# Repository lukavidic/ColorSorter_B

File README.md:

# Color Sorter | Real-Time Tile Sorting 🟥🟩🟦

## Project Specification

The project owner has defined the following general requirements:

- Detect and sort tiles by color using a sensor-based system.  
- Develop a PC application that provides Wi-Fi communication, real-time visualization, and process control.  
- Include a local physical interface for basic start/stop control.

## Project Objective

The goal of this project is to sort colored tiles into two designated containers. The system includes:

- **PIC24FJ64GA702 MCU** on a custom PCB,  
- **Color 10 Click sensor** for color detection,  
- **SG90 servo motor** to direct each tile into its container,  
- **ESP8266-01 Wi-Fi module** for wireless link to PC,  
- **Push-button** to toggle the sorting cycle on/off,  
- **LED indicator** to show system status.  

When a tile passes under the Color 10 Click sensor, it measures the color and sends the data via I²C to the MCU.

Based on the sorting logic, the MCU drives the servo to move the tile into the correct container.

The push-button starts and stops the cycle, while the LED indicates whether the system is active.

A PC application offers a graphical interface for live monitoring and control. It communicates with the ESP8266-01 over Wi-Fi, which forwards commands to the microcontroller using UART protocol.

## Additional Information

For detailed component specifications, wiring diagrams, datasheets and code documentation please see the Wiki pages in this repository.

## Project Video Presentation

[Video](https://github.com/lukavidic/ColorSorter_B/blob/project/video/ColorSorterB.mp4)

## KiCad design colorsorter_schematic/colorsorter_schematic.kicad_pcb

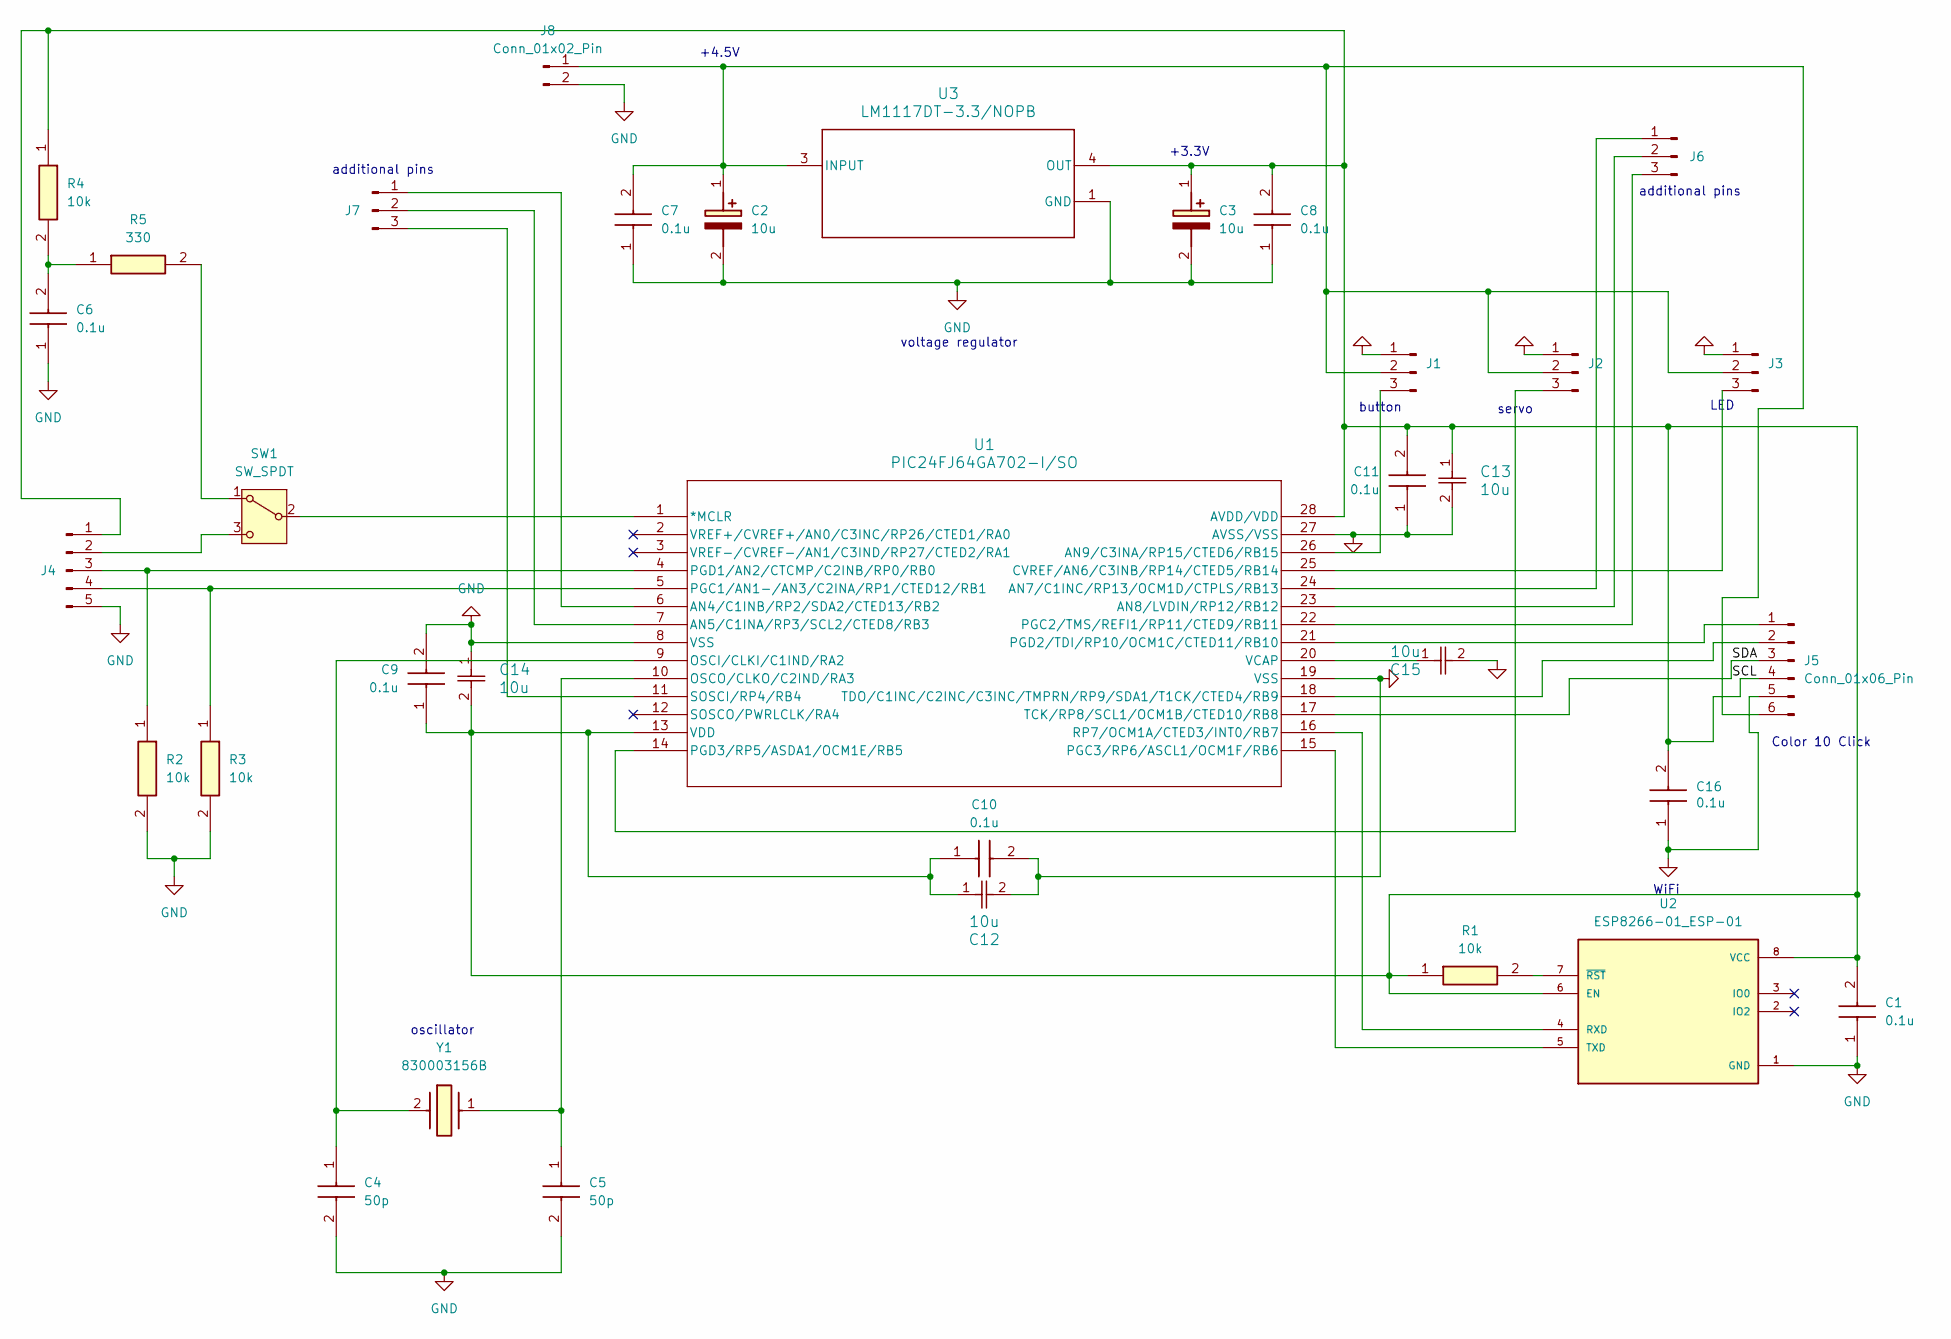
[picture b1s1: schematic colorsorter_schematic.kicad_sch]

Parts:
C1, C6, C7, C8, C9, C10, C11, C16: 0.1u; CAPC2012X94N; Manufacturer_Part_Number KAM21BR71H104JT; Mouser Part Number 581-KAM21BR71H104JT
C2, C3: 10u; CAPPM6032X280N; Manufacturer_Part_Number 293D106X9010C2TE3; Mouser Part Number 74-293D106X9010C2TE3
C4, C5: 50p; CAPC2012X140N; Manufacturer_Part_Number 08055A500FAT2A; Mouser Part Number 581-08055A500FAT2A
C12, C13, C14, C15: 10u; CAP_2012_TDK
J1, J2, J3, J6, J7: Conn_01x03_Pin; PinHeader_1x03_P2.54mm_Vertical
J4: Conn_01x05_Pin; PinHeader_1x05_P2.54mm_Vertical
J5: Conn_01x06_Pin; PinHeader_1x06_P2.54mm_Vertical
J8: Conn_01x02_Pin; PinHeader_1x02_P2.54mm_Vertical
R1, R2, R3, R4: 10k; RESC2012X70N; Manufacturer_Part_Number ERJ-S06F1002V; Mouser Part Number 667-ERJ-S06F1002V
R5: 330; ERJP06D1000V; Manufacturer_Part_Number ERJ-P06D3300V; Mouser Part Number 667-ERJ-P06D3300V
SW1: SW_SPDT; SLW12768644AD
U1: PIC24FJ64GA702-I/SO; SOIC28__SO28_MCH
U2: ESP8266-01_ESP-01; wifi; PARTREV V1.2
U3: LM1117DT-3.3/NOPB; NDP0003B
Y1: 830003156B; Manufacturer_Part_Number 830003156B; Mouser Part Number 710-830003156B

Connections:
/SCL: J5.3, U1.17 (TCK/RP8/SCL1/OCM1B/CTED10/RB8); also elsewhere on the board
GND: C1.1, C2.2 (-), C3.2 (-), C4.2, C5.2, C6.1, C7.1, C8.1, C9.2, C10.2, C11.1, C12.2, C13.2, C14.1, C15.2, C16.1, J1.1, J2.1, J3.1, J4.5, J5.5, J8.2, R2.2, R3.2, U1.8 (VSS), U1.19 (VSS), U1.27 (AVSS/VSS), U2.1 (GND), U3.1 (GND); also elsewhere on the board
unnamed: C2.1 (+), C7.2, J1.2, J2.2, J3.2, J5.6, J8.1, U3.3 (INPUT)
unnamed 3: C1.2, C3.1 (+), C8.2, C9.1, C10.1, C11.2, C12.1, C13.1, C14.2, C16.2, J4.1, J5.4, R1.1, R4.1, U1.13 (VDD), U1.28 (AVDD/VDD), U2.6 (EN), U2.8 (VCC), U3.4 (OUT); also elsewhere on the board
unnamed: C6.2, R4.2, R5.1
unnamed 5: J1.3, U1.26 (AN9/C3INA/RP15/CTED6/RB15); also elsewhere on the board
unnamed 6: J2.3, U1.14 (PGD3/RP5/ASDA1/OCM1E/RB5); also elsewhere on the board
unnamed 7: J3.3, U1.25 (CVREF/AN6/C3INB/RP14/CTED5/RB14); also elsewhere on the board
unnamed: J4.2, SW1.3 (C)
unnamed 9: J4.3, R2.1, U1.4 (PGD1/AN2/CTCMP/C2INB/RP0/RB0); also elsewhere on the board
unnamed 10: J4.4, R3.1, U1.5 (PGC1/AN1-/AN3/C2INA/RP1/CTED12/RB1); also elsewhere on the board
unnamed 11: J5.1, U1.21 (PGD2/TDI/RP10/OCM1C/CTED11/RB10); also elsewhere on the board
unnamed 12: J5.2, U1.18 (TDO/C1INC/C2INC/C3INC/TMPRN/RP9/SDA1/T1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); also elsewhere on the board
unnamed 13: J6.1, U1.24 (AN7/C1INC/RP13/OCM1D/CTPLS/RB13); also elsewhere on the board
unnamed 14: J6.2, U1.23 (AN8/LVDIN/RP12/RB12); also elsewhere on the board
unnamed 15: J6.3, U1.22 (PGC2/TMS/REFI1/RP11/CTED9/RB11); also elsewhere on the board
unnamed 16: J7.1, U1.6 (AN4/C1INB/RP2/SDA2/CTED13/RB2); also elsewhere on the board
unnamed 17: J7.2, U1.7 (AN5/C1INA/RP3/SCL2/CTED8/RB3); also elsewhere on the board
unnamed 18: J7.3, U1.11 (SOSCI/RP4/RB4); also elsewhere on the board
unnamed: R5.2, SW1.1 (A)
unnamed 20: SW1.2 (B), U1.1 (*MCLR); also elsewhere on the board
unnamed 21: C4.1, U1.9 (OSCI/CLKI/C1IND/RA2), Y1.2 (CRYSTAL_2); also elsewhere on the board
unnamed 22: C5.1, U1.10 (OSCO/CLKO/C2IND/RA3), Y1.1; also elsewhere on the board
unnamed 23: U1.15 (PGC3/RP6/ASCL1/OCM1F/RB6), U2.5 (TXD); also elsewhere on the board
unnamed 24: U1.16 (RP7/OCM1A/CTED3/INT0/RB7), U2.4 (RXD); also elsewhere on the board
unnamed 25: C15.1, U1.20 (VCAP); also elsewhere on the board
unnamed: R1.2, U2.7 (~RST)

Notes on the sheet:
additional pins
LED
oscillator
+3.3V
+4.5V
servo
WiFi
voltage regulator
button
Color 10 Click

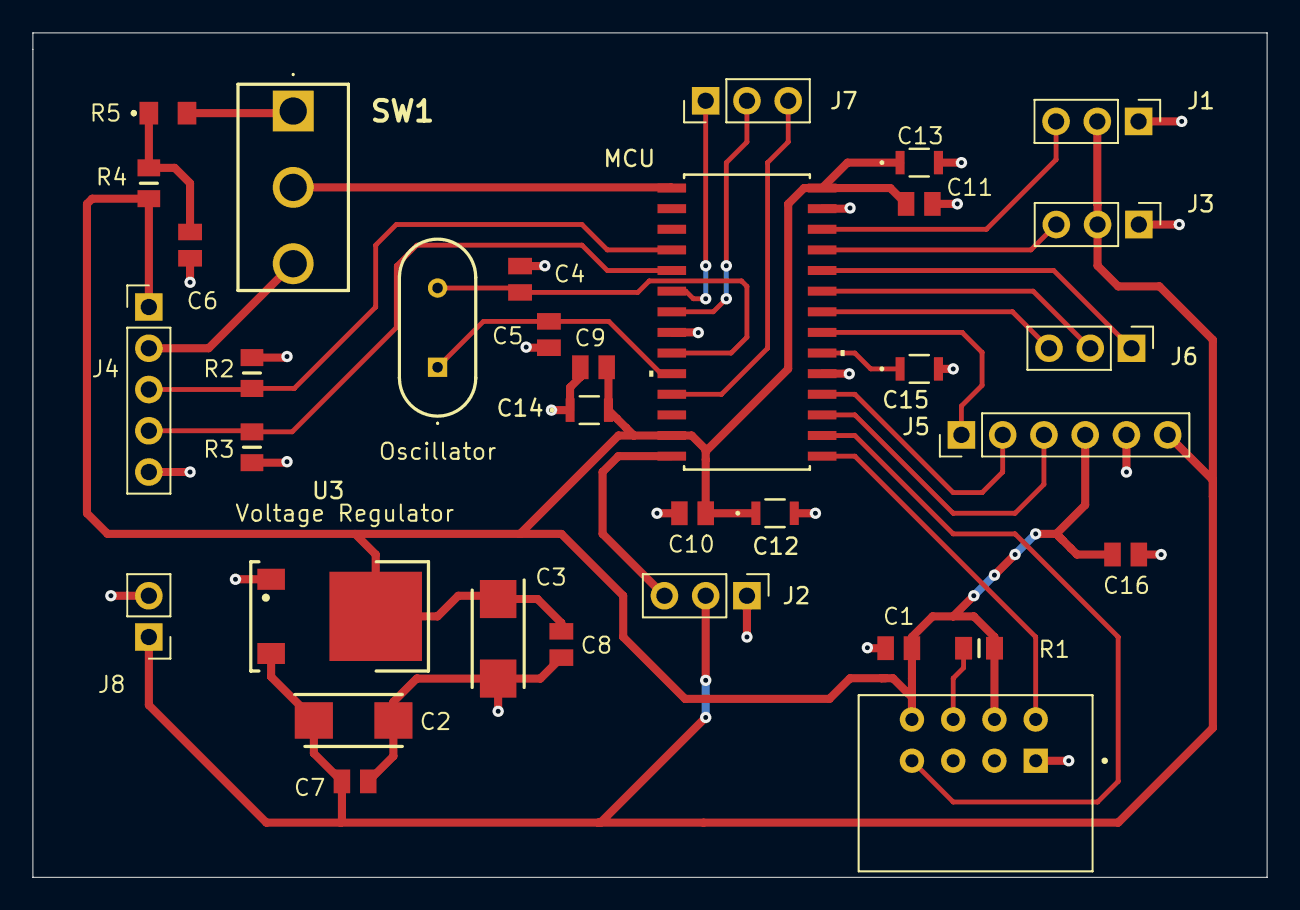
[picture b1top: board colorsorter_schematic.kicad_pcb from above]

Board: 2 copper layers, 76.0 x 52.0 mm, 34 parts (0 on the bottom side), 27 nets.

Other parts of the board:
MCU: PIC24FJ64GA702-I/SO; SOIC28__SO28_MCH
Oscillator: 830003156B

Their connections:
/SCL: MCU.17 (TCK/RP8/SCL1/OCM1B/CTED10/RB8); also elsewhere on the board
GND: MCU.8 (VSS), MCU.19 (VSS), MCU.27 (AVSS/VSS); also elsewhere on the board
unnamed 3: MCU.13 (VDD), MCU.28 (AVDD/VDD); also elsewhere on the board
unnamed 5: MCU.26 (AN9/C3INA/RP15/CTED6/RB15); also elsewhere on the board
unnamed 6: MCU.14 (PGD3/RP5/ASDA1/OCM1E/RB5); also elsewhere on the board
unnamed 7: MCU.25 (CVREF/AN6/C3INB/RP14/CTED5/RB14); also elsewhere on the board
unnamed 9: MCU.4 (PGD1/AN2/CTCMP/C2INB/RP0/RB0); also elsewhere on the board
unnamed 10: MCU.5 (PGC1/AN1-/AN3/C2INA/RP1/CTED12/RB1); also elsewhere on the board
unnamed 11: MCU.21 (PGD2/TDI/RP10/OCM1C/CTED11/RB10); also elsewhere on the board
unnamed 12: MCU.18 (TDO/C1INC/C2INC/C3INC/TMPRN/RP9/SDA1/T1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); also elsewhere on the board
unnamed 13: MCU.24 (AN7/C1INC/RP13/OCM1D/CTPLS/RB13); also elsewhere on the board
unnamed 14: MCU.23 (AN8/LVDIN/RP12/RB12); also elsewhere on the board
unnamed 15: MCU.22 (PGC2/TMS/REFI1/RP11/CTED9/RB11); also elsewhere on the board
unnamed 16: MCU.6 (AN4/C1INB/RP2/SDA2/CTED13/RB2); also elsewhere on the board
unnamed 17: MCU.7 (AN5/C1INA/RP3/SCL2/CTED8/RB3); also elsewhere on the board
unnamed 18: MCU.11 (SOSCI/RP4/RB4); also elsewhere on the board
unnamed 20: MCU.1 (*MCLR); also elsewhere on the board
unnamed 21: MCU.9 (OSCI/CLKI/C1IND/RA2), Oscillator.2 (CRYSTAL_2); also elsewhere on the board
unnamed 22: MCU.10 (OSCO/CLKO/C2IND/RA3), Oscillator.1; also elsewhere on the board
unnamed 23: MCU.15 (PGC3/RP6/ASCL1/OCM1F/RB6); also elsewhere on the board
unnamed 24: MCU.16 (RP7/OCM1A/CTED3/INT0/RB7); also elsewhere on the board
unnamed 25: MCU.20 (VCAP); also elsewhere on the board

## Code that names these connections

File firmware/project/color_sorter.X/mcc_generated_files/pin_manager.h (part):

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*/
/**
  @Summary
    Sets the GPIO pin, RB10, high using LATB10.

  @Description
    Sets the GPIO pin, RB10, high using LATB10.

  @Preconditions
    The RB10 must be set to an output.
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#define SDO1_SetHigh()          (_LATB10 = 1)
/**
  @Summary
    Sets the GPIO pin, RB10, low using LATB10.

  @Description
    Sets the GPIO pin, RB10, low using LATB10.

  @Preconditions
    The RB10 must be set to an output.
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#define SDO1_SetLow()           (_LATB10 = 0)
/**
  @Summary
    Toggles the GPIO pin, RB10, using LATB10.

  @Description
    Toggles the GPIO pin, RB10, using LATB10.

  @Preconditions
    The RB10 must be set to an output.
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#define SDO1_Toggle()           (_LATB10 ^= 1)
/**
  @Summary
    Reads the value of the GPIO pin, RB10.

  @Description
    Reads the value of the GPIO pin, RB10.

  @Preconditions
    None.
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    </code>

*/
#define SDO1_GetValue()         _RB10
/**
  @Summary
    Configures the GPIO pin, RB10, as an input.

  @Description
    Configures the GPIO pin, RB10, as an input.

  @Preconditions
    None.
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#define SDO1_SetDigitalInput()  (_TRISB10 = 1)
/**
  @Summary
    Configures the GPIO pin, RB10, as an output.

  @Description
    Configures the GPIO pin, RB10, as an output.

  @Preconditions
    None.
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#define SDO1_SetDigitalOutput() (_TRISB10 = 0)
/**
  @Summary
    Sets the GPIO pin, RB11, high using LATB11.

  @Description
    Sets the GPIO pin, RB11, high using LATB11.

  @Preconditions
    The RB11 must be set to an output.
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#define SCK1OUT_SetHigh()          (_LATB11 = 1)
/**
  @Summary
    Sets the GPIO pin, RB11, low using LATB11.

  @Description
    Sets the GPIO pin, RB11, low using LATB11.

  @Preconditions
    The RB11 must be set to an output.
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#define SCK1OUT_SetLow()           (_LATB11 = 0)
/**
  @Summary
    Toggles the GPIO pin, RB11, using LATB11.

  @Description
    Toggles the GPIO pin, RB11, using LATB11.

  @Preconditions
    The RB11 must be set to an output.
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#define SCK1OUT_Toggle()           (_LATB11 ^= 1)
/**
  @Summary
    Reads the value of the GPIO pin, RB11.

  @Description
    Reads the value of the GPIO pin, RB11.

  @Preconditions
    None.
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    </code>

*/
#define SCK1OUT_GetValue()         _RB11
/**
  @Summary
    Configures the GPIO pin, RB11, as an input.

  @Description
    Configures the GPIO pin, RB11, as an input.

  @Preconditions
    None.
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#define SCK1OUT_SetDigitalInput()  (_TRISB11 = 1)
/**
  @Summary
    Configures the GPIO pin, RB11, as an output.

  @Description
    Configures the GPIO pin, RB11, as an output.

  @Preconditions
    None.
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#define SCK1OUT_SetDigitalOutput() (_TRISB11 = 0)
/**
  @Summary
    Sets the GPIO pin, RB14, high using LATB14.

  @Description
    Sets the GPIO pin, RB14, high using LATB14.

  @Preconditions
    The RB14 must be set to an output.
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#define IO_RB14_SetHigh()          (_LATB14 = 1)
/**
  @Summary
    Sets the GPIO pin, RB14, low using LATB14.

  @Description
    Sets the GPIO pin, RB14, low using LATB14.

  @Preconditions
    The RB14 must be set to an output.
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#define IO_RB14_SetLow()           (_LATB14 = 0)
/**
  @Summary
    Toggles the GPIO pin, RB14, using LATB14.

  @Description
    Toggles the GPIO pin, RB14, using LATB14.

  @Preconditions
    The RB14 must be set to an output.
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#define IO_RB14_Toggle()           (_LATB14 ^= 1)
/**
  @Summary
    Reads the value of the GPIO pin, RB14.

  @Description
    Reads the value of the GPIO pin, RB14.

  @Preconditions
    None.
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    </code>

*/
#define IO_RB14_GetValue()         _RB14
/**
  @Summary
    Configures the GPIO pin, RB14, as an input.

  @Description
    Configures the GPIO pin, RB14, as an input.

  @Preconditions
    None.
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#define IO_RB14_SetDigitalInput()  (_TRISB14 = 1)
/**
  @Summary
    Configures the GPIO pin, RB14, as an output.

  @Description
    Configures the GPIO pin, RB14, as an output.

  @Preconditions
    None.
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#define IO_RB14_SetDigitalOutput() (_TRISB14 = 0)
/**
  @Summary
    Sets the GPIO pin, RB15, high using LATB15.

  @Description
    Sets the GPIO pin, RB15, high using LATB15.

  @Preconditions
    The RB15 must be set to an output.
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#define IO_RB15_SetHigh()          (_LATB15 = 1)
/**
  @Summary
    Sets the GPIO pin, RB15, low using LATB15.

  @Description
    Sets the GPIO pin, RB15, low using LATB15.

  @Preconditions
    The RB15 must be set to an output.
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#define IO_RB15_SetLow()           (_LATB15 = 0)
/**
  @Summary
    Toggles the GPIO pin, RB15, using LATB15.

  @Description
    Toggles the GPIO pin, RB15, using LATB15.

  @Preconditions
    The RB15 must be set to an output.
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#define IO_RB15_Toggle()           (_LATB15 ^= 1)
/**
  @Summary
    Reads the value of the GPIO pin, RB15.

  @Description
    Reads the value of the GPIO pin, RB15.

  @Preconditions
    None.
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    </code>

*/
#define IO_RB15_GetValue()         _RB15
/**
  @Summary
    Configures the GPIO pin, RB15, as an input.

  @Description
    Configures the GPIO pin, RB15, as an input.

  @Preconditions
    None.
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#define IO_RB15_SetDigitalInput()  (_TRISB15 = 1)
/**
  @Summary
    Configures the GPIO pin, RB15, as an output.

  @Description
    Configures the GPIO pin, RB15, as an output.

  @Preconditions
    None.
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#define IO_RB15_SetDigitalOutput() (_TRISB15 = 0)
/**
  @Summary
    Sets the GPIO pin, RB5, high using LATB5.

  @Description
    Sets the GPIO pin, RB5, high using LATB5.

  @Preconditions
    The RB5 must be set to an output.
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#define IO_RB5_SetHigh()          (_LATB5 = 1)
/**
  @Summary
    Sets the GPIO pin, RB5, low using LATB5.

  @Description
    Sets the GPIO pin, RB5, low using LATB5.

  @Preconditions
    The RB5 must be set to an output.
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#define IO_RB5_SetLow()           (_LATB5 = 0)
/**
  @Summary
    Toggles the GPIO pin, RB5, using LATB5.

  @Description
    Toggles the GPIO pin, RB5, using LATB5.

  @Preconditions
    The RB5 must be set to an output.
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#define IO_RB5_Toggle()           (_LATB5 ^= 1)
/**
  @Summary
    Reads the value of the GPIO pin, RB5.

  @Description
    Reads the value of the GPIO pin, RB5.

  @Preconditions
    None.
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    </code>

*/
#define IO_RB5_GetValue()         _RB5
/**
  @Summary
    Configures the GPIO pin, RB5, as an input.

  @Description
    Configures the GPIO pin, RB5, as an input.

  @Preconditions
    None.
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#define IO_RB5_SetDigitalInput()  (_TRISB5 = 1)
/**
  @Summary
    Configures the GPIO pin, RB5, as an output.

  @Description
    Configures the GPIO pin, RB5, as an output.

  @Preconditions
    None.
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
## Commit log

2024-11-26 Add docs folder with datasheet files
2024-11-27 Add images folder
2024-11-27 Added button image
2024-11-27 Added Led Diode image
2024-12-03 Color 10 Click picture added for Wiki.
2024-12-03 Resized Color 10 Click picture.
2024-12-03 WiFi module picture added for Wiki.
2024-12-03 Adding pdfs/images
2024-12-03 Resized pictures for Wiki.
2024-12-03 Added files for Wi-Fi Module Wiki.
2024-12-03 Resized picture for Wi-Fi module Wiki.
2024-12-04 Added mcu pin diagram for Wiki.
2024-12-04 Added Wi-Fi_pinouts picture for Wiki.
2024-12-04 Added Servo motor picture for Wiki.
2024-12-10 Issue #11 and #16: Added KiCad files.
2024-12-10 Issue #10 : Projektovanje električne šeme - minimalni broj pinova
2024-12-10 Issue #14 : Projektovanje električne šeme - taster
2024-12-10 Simbols and footprints used in KiCad.
2024-12-10 Issue #13 : Projektovanje električne šeme - servo motor
2024-12-10 Issue #18:
2024-12-10 Issue #18: Projektovanje elektricne seme-LED
2024-12-10 Issue #17 : Projektovanje električne šeme - naponski regulator - potencijalna komponenta.
2024-12-11 Added pdf and image for PICkit 3
2024-12-11 Issue #15 : Konfiguracija oscilatora
2024-12-18 Popravke na semi.
2024-12-25 Added oscillator and voltage regulator datasheets.
2024-12-25 Deleted unused files from voltage_regulator directory
2024-12-25 Added capacitors, resistors, voltage regulator and oscillator symbols and footprints.
2024-12-25 Added voltage regulator, oscillator and bulk capacitors.
2024-12-25 Correction - added ground to WiFi module pin.
2024-12-25 Added additional pins header.
2025-01-15 Dodavanje izmjena u semi i rutranje na pcb
2025-01-15 Updated schematic.
2025-01-15 Updated schematic and pcb.
2025-01-15 Schematics Updated 15/1/2025
2025-01-16 Popravljena verzija pcb-a.
2025-01-23 J5 conn changed from 5 pin to 6 pin - updated pcb
2025-01-23 J5 conn changed from 5 pin to 6 pin - updated pcb - saved changes
2025-01-23 Dodavanje izmjena na pcb projekta
2025-01-28 Dodavanje izmjena na pcb fajlu.
2025-01-28 Final version PCB and manufacturing files
2025-01-30 Added manufaturing and fabrication files
2025-02-12 Dodavanje tekstualnih izmjena na semi.
2025-02-16 Images used for electrical schematic documentation.
2025-02-16 Images used for PCB documentation.
2025-03-04 Issue #21: .c and .hex files for initial testing
2025-03-20 Issue #22: Testiranje povezivanja servo motora sa mikrokontrolerom
    Added testing code for servo functionality to verify PWM output and angle mapping
2025-04-22 Added Java application code
2025-04-29 Dodavanje README.md fajla sa osnovnim opisom sistema.
2025-05-02 WS2812.PDF datasheet added for Wiki page
2025-05-02 Issue #23: Color sensor reading - test program with calibration.
2025-05-06 Project final version.
2025-05-07 Add video file via Git LFS
2025-05-07 Issue #25: Dokumentacija Firmware i Application code
    Added documentation for the project Firmware
2025-05-07 Issue #25: Dokumentacija Firmware i Application code
    Added documentation for the project Application
2025-05-08 Changes to the wiki page Electrical Schematic Design

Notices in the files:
firmware/project/color_sorter.X/mcc_generated_files/pin_manager.h:
(c) 2020 Microchip Technology Inc. and its subsidiaries. You may use this
